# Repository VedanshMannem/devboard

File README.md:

# Devboard
This project contains all the files of my first devboard. This is great for electronics engineering and hobbyists, with a USBC and RP2040. I included LEDs on this board to make it more flashy, as well as silkscreen art to make it personal. The full BOMs are attached (there's two - one from JLCPCB and one from KiCAD). 

## Setup
All the KiCAD project files are available in the KiCAD folder, and there's photos of the devboard included as well for a rough outline of the end product. Hardest part of this project is honeslty the routing, but as long as you place all the components in the right place, the routing shouldn't be that bad. I went through a few versions of the board to make sure the routing was just right. Try to save the vias for the end as well, its just better practice and I think the board will look less messy without them. 

Here's some photos:

Overall, learned a ton because this was my first full scale PCB project. Thanks for reading!

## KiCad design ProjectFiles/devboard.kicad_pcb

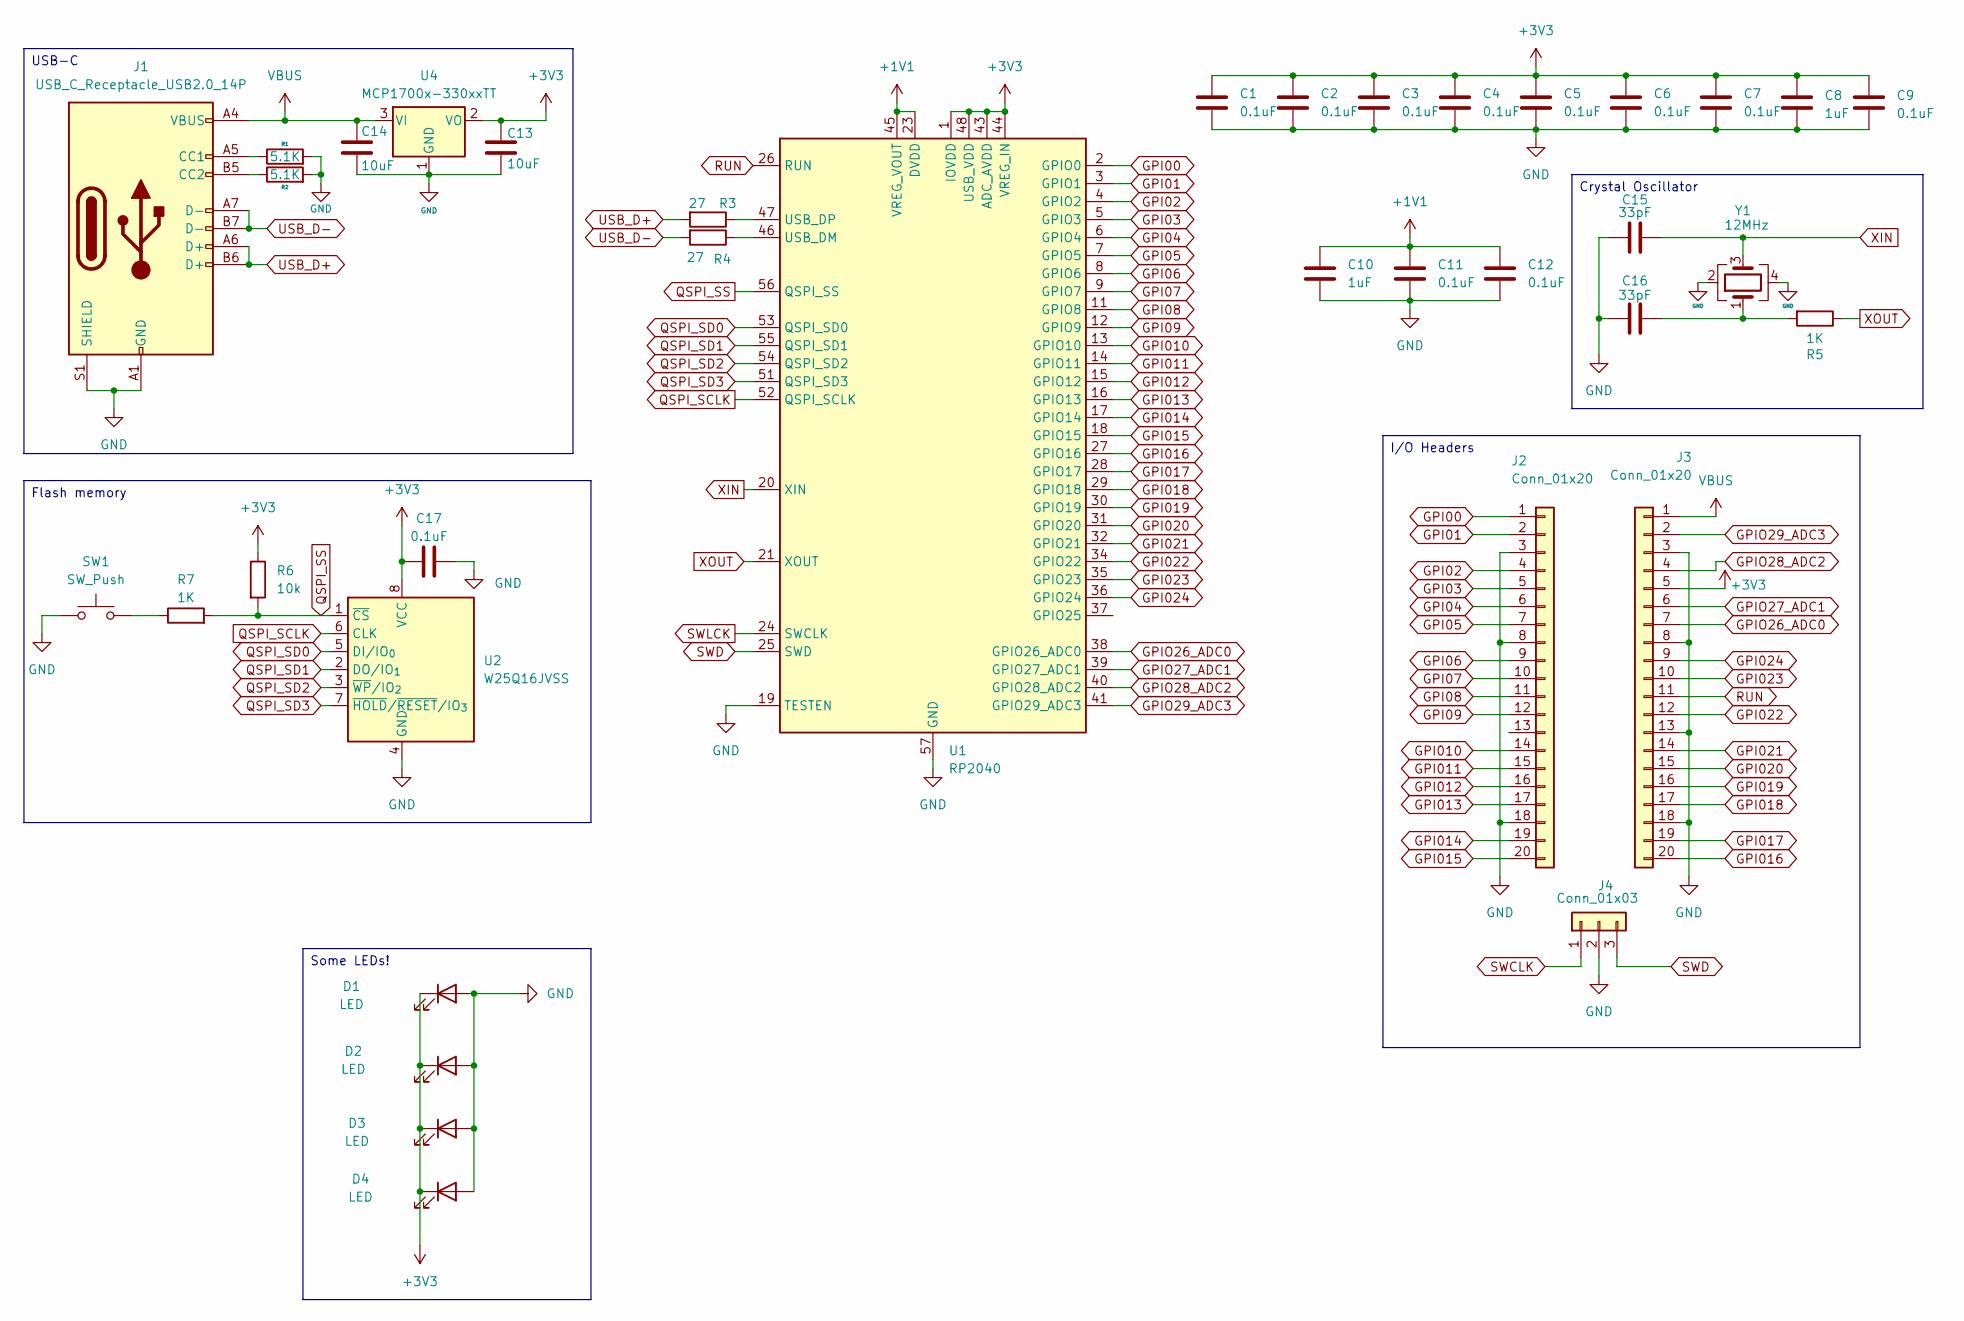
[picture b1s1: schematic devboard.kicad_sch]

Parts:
C1, C2, C3, C4, C5, C6, C7, C9, C11, C12, C17: 0.1uF; C_0402_1005Metric
C8, C10: 1uF; C_0402_1005Metric
C13, C14: 10uF; C_0402_1005Metric
C15, C16: 33pF; C_0402_1005Metric
D1, D2, D3, D4: LED; LED_0402_1005Metric_Pad0.77x0.64mm_HandSolder
J1: USB_C_Receptacle_USB2.0_14P; USB_C_Receptacle_HRO_TYPE-C-31-M-12
J2, J3: Conn_01x20; PinHeader_1x20_P2.54mm_Vertical
J4: Conn_01x03; PinHeader_1x03_P2.54mm_Vertical
R1, R2: 5.1K; R_0402_1005Metric
R3, R4: 27; R_0402_1005Metric
R5, R7: 1K; R_0402_1005Metric
R6: 10k; R_0402_1005Metric
SW1: SW_Push; SW_Push_SPST_NO_Alps_SKRK
U1: RP2040; QFN-56-1EP_7x7mm_P0.4mm_EP3.2x3.2mm
U2: W25Q16JVSS; Winbond_USON-8-1EP_3x2mm_P0.5mm_EP0.2x1.6mm
U4: MCP1700x-330xxTT; SOT-23
Y1: 12MHz; Crystal_SMD_3225-4Pin_3.2x2.5mm

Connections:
+1V1: C10.1, C11.1, C12.1, U1.23 (DVDD), U1.45 (VREG_VOUT), U1.50 (DVDD)
+3V3: C1.1, C2.1, C3.1, C4.1, C5.1, C6.1, C7.1, C8.1, C9.1, C13.1, C17.1, D1.1 (K), D2.1 (K), D3.1 (K), D4.1 (K), J3.5, R6.1, U1.1 (IOVDD), U1.10 (IOVDD), U1.22 (IOVDD), U1.33 (IOVDD), U1.42 (IOVDD), U1.43 (ADC_AVDD), U1.44 (VREG_IN), U1.48 (USB_VDD), U1.49 (IOVDD), U2.8 (VCC), U4.2 (VO)
GND: C1.2, C2.2, C3.2, C4.2, C5.2, C6.2, C7.2, C8.2, C9.2, C10.2, C11.2, C12.2, C13.2, C14.2, C15.1, C16.1, C17.2, D1.2 (A), D2.2 (A), D3.2 (A), D4.2 (A), J1.A1 (GND), J1.A12 (GND), J1.B1 (GND), J1.B12 (GND), J1.S1 (SHIELD), J2.3, J2.8, J2.18, J3.3, J3.8, J3.13, J3.18, J4.2, R1.2, R2.2, SW1.1, U1.19 (TESTEN), U1.57 (GND), U2.4 (GND), U4.1 (GND), Y1.2, Y1.4
GPI00: J2.1, U1.2 (GPIO0)
GPI01: J2.2, U1.3 (GPIO1)
GPI02: J2.4, U1.4 (GPIO2)
GPI03: J2.5, U1.5 (GPIO3)
GPI04: J2.6, U1.6 (GPIO4)
GPI05: J2.7, U1.7 (GPIO5)
GPI06: J2.9, U1.8 (GPIO6)
GPI07: J2.10, U1.9 (GPIO7)
GPI08: J2.11, U1.11 (GPIO8)
GPI09: J2.12, U1.12 (GPIO9)
GPI010: J2.14, U1.13 (GPIO10)
GPI011: J2.15, U1.14 (GPIO11)
GPI012: J2.16, U1.15 (GPIO12)
GPI013: J2.17, U1.16 (GPIO13)
GPI014: J2.19, U1.17 (GPIO14)
GPI015: J2.20, U1.18 (GPIO15)
GPI016: J3.20, U1.27 (GPIO16)
GPI017: J3.19, U1.28 (GPIO17)
GPI018: J3.17, U1.29 (GPIO18)
GPI019: J3.16, U1.30 (GPIO19)
GPI020: J3.15, U1.31 (GPIO20)
GPI021: J3.14, U1.32 (GPIO21)
GPI022: J3.12, U1.34 (GPIO22)
GPI023: J3.10, U1.35 (GPIO23)
GPI024: J3.9, U1.36 (GPIO24)
GPIO26_ADC0: J3.7, U1.38 (GPIO26_ADC0)
GPIO27_ADC1: J3.6, U1.39 (GPIO27_ADC1)
GPIO28_ADC2: J3.4, U1.40 (GPIO28_ADC2)
GPIO29_ADC3: J3.2, U1.41 (GPIO29_ADC3)
unnamed: C16.2, R5.2, Y1.1
unnamed: J1.A5 (CC1), R1.1
unnamed: J1.B5 (CC2), R2.1
unnamed: R7.1, SW1.2
unnamed: R4.1, U1.46 (USB_DM)
unnamed: R3.1, U1.47 (USB_DP)
QSPI_SCLK: U1.52 (QSPI_SCLK), U2.6 (CLK)
QSPI_SD0: U1.53 (QSPI_SD0), U2.5 (DI/IO_{0})
QSPI_SD1: U1.55 (QSPI_SD1), U2.2 (DO/IO_{1})
QSPI_SD2: U1.54 (QSPI_SD2), U2.3 (~WP/IO_{2})
QSPI_SD3: U1.51 (QSPI_SD3), U2.7 (~HOLD/~RESET/IO_{3})
QSPI_SS: R6.2, R7.2, U1.56 (QSPI_SS), U2.1 (~CS)
RUN: J3.11, U1.26 (RUN)
SWCLK: J4.1
SWD: J4.3, U1.25 (SWD)
SWLCK: U1.24 (SWCLK)
USB_D+: J1.A6 (D+), J1.B6 (D+), R3.2
USB_D-: J1.A7 (D-), J1.B7 (D-), R4.2
VBUS: C14.1, J1.A4 (VBUS), J1.A9 (VBUS), J1.B4 (VBUS), J1.B9 (VBUS), J3.1, U4.3 (VI)
XIN: C15.2, U1.20 (XIN), Y1.3
XOUT: R5.1, U1.21 (XOUT)

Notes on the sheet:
I/O Headers
USB-C
Crystal Oscillator
Flash memory
Some LEDs!

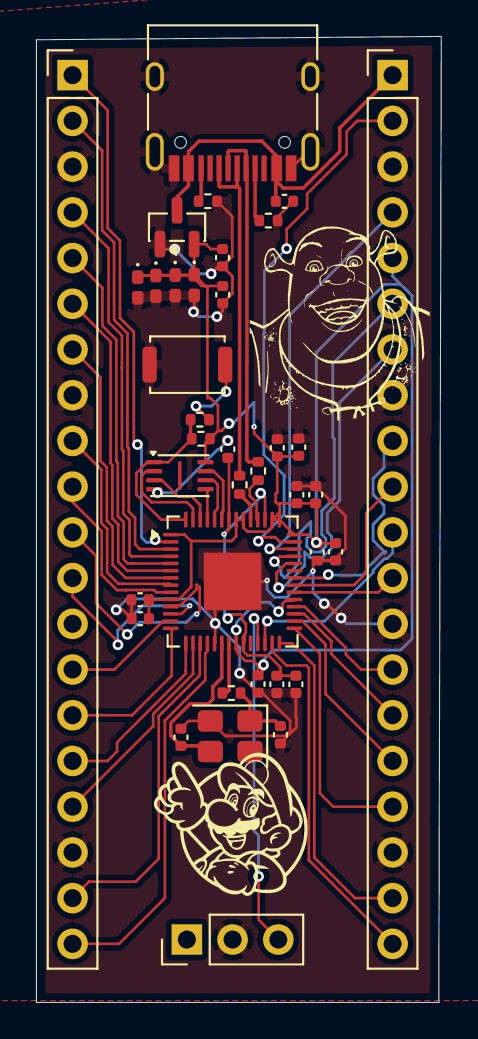
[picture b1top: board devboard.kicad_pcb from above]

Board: 2 copper layers, 22.5 x 53.7 mm, 37 parts (0 on the bottom side), 51 nets.

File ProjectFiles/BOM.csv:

Id,Designator,Footprint,Quantity,Comment,Supplier and ref
1,"C15,C16",C_0402_1005Metric,2,33pF,
2,U1,QFN-56-1EP_7x7mm_P0.4mm_EP3.2x3.2mm,1,RP2040,
3,"C7,C12,C11,C6,C2,C9,C1,C4,C3,C17,C5",C_0402_1005Metric,11,0.1uF,
4,SW1,SW_Push_SPST_NO_Alps_SKRK,1,SW_Push,
5,"C14,C13",C_0402_1005Metric,2,10uF,
6,U2,Winbond_USON-8-1EP_3x2mm_P0.5mm_EP0.2x1.6mm,1,W25Q16JVSS,
7,"J2,J3",PinHeader_1x20_P2.54mm_Vertical,2,Conn_01x20,
8,R6,R_0402_1005Metric,1,10k,
9,J4,PinHeader_1x03_P2.54mm_Vertical,1,Conn_01x03,
10,"D3,D2,D1,D4",LED_0402_1005Metric_Pad0.77x0.64mm_HandSolder,4,LED,
11,"R2,R1",R_0402_1005Metric,2,5.1K,
12,"R4,R3",R_0402_1005Metric,2,27,
13,U4,SOT-23,1,MCP1700x-330xxTT,
14,"C10,C8",C_0402_1005Metric,2,1uF,
15,"R5,R7",R_0402_1005Metric,2,1K,
16,Y1,Crystal_SMD_3225-4Pin_3.2x2.5mm,1,12MHz,
17,J1,USB_C_Receptacle_HRO_TYPE-C-31-M-12,1,USB_C_Receptacle_USB2.0_14P,

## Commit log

2025-11-28 Add placeholder.txt with initial content
2025-11-28 kiCad files upload
2025-11-28 Add project description and images to README
    This project contains all the files of my very own devboard, which is great for engineering and hobbyists, featuring silkscreen art and added LEDs. It includes two BOMs and showcases various photos o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
2025-11-30 Revise README with project details and setup info
    Updated project description and added setup instructions.
